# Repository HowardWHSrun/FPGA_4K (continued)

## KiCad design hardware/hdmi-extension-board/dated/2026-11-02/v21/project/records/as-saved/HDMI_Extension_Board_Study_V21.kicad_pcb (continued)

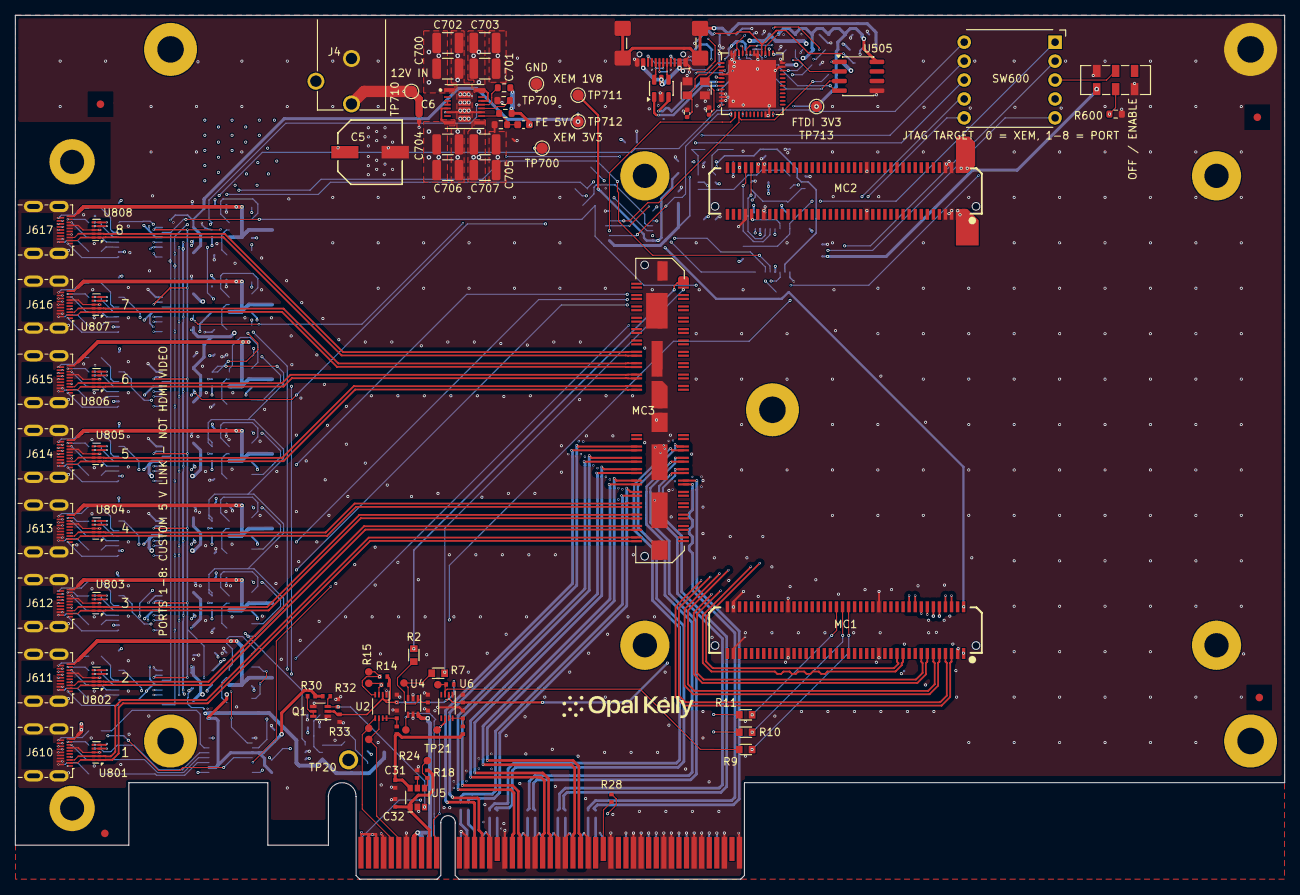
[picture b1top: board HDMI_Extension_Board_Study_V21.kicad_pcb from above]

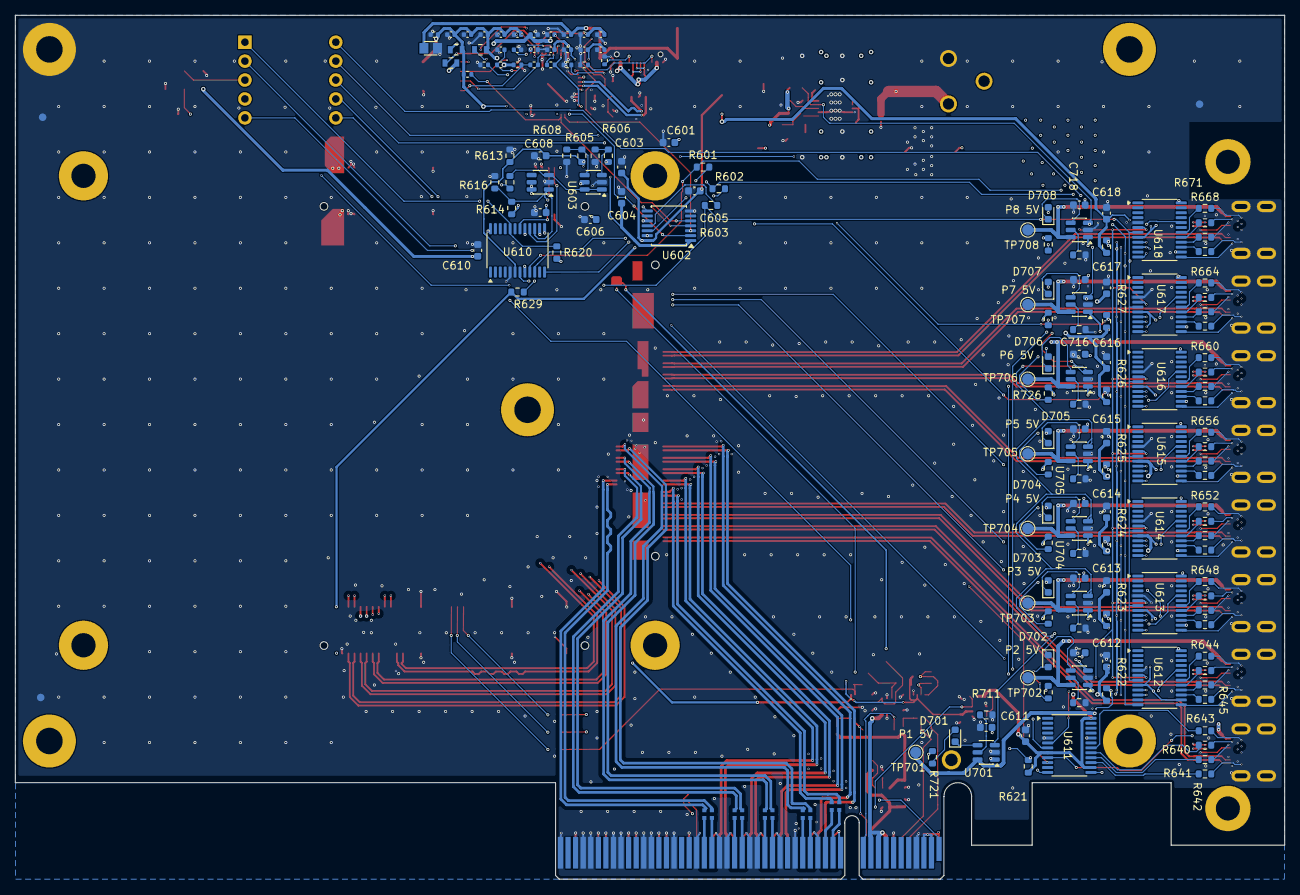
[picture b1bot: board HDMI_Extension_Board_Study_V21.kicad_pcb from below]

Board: 6 copper layers, 167.6 x 114.1 mm, 275 parts (173 on the bottom side), 254 nets.

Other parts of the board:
*: Opal Kelly Logo; BRK_Logo_c689e08d
FID1, FID5, FID6, FID7: FIDUCIAL; BRK_FID1
FID2: FIDUCIAL; BRK_FID2
FID3: FIDUCIAL; BRK_FID3
FID4: FIDUCIAL; BRK_FID4

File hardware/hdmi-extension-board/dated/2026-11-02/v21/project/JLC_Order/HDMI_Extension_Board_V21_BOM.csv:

Comment,Designator,Footprint,JLCPCB Part #
C0402C104K8PACTU,"C7,C8,C9,C10,C11,C12,C13,C14,C15,C16,C17,C18,C19,C20,C27,C28,C31,C32,C501,C502,C505,C508,C509,C510,C511,C514,C516,C517,C518",BRK8310_C10,C2649544
EEE-FK1E221P,C5,BRK_C5,C128511
4.7u,C500,C500,C23733
18p,"C503,C504",C504,C22442494
100n,C506,C506,C1525
4.7u,"C507,C512,C513,C515",C515,C87147
10n,C519,C519,C2649513
TMK105BJ104KV-F,C6,BRK_C6,C77014
2.2u,"C601,C603",C_0603_1608Metric,C100082
100nF,"C604,C605,C606,C609,C610,C611,C612,C613,C614,C615,C616,C617,C618,C711,C712,C713,C714,C715,C716,C717,C718",C_0603_1608Metric,C14663
1n,C608,C_0603_1608Metric,C8808
10uF,"C700,C701,C702,C703",C_1210_3225Metric,C77102
47uF,"C704,C705,C706,C707",C_1210_3225Metric,C77101
22pF,C708,C_0603_1608Metric,C376775
USBLC6-2SC6,D500,D500,C7519
RED,"D701,D702,D703,D704,D705,D706,D707,D708",LED_0603_1608Metric,C94869
600R,"FB500,FB501,FB502",FB502,C19330
220R @100MHz,FB503,FB503,C85840
PJ-102AH,J4,BRK_J4,C3096093
USB4110-GF-A,J500,J500,C5143397
467651001,"J610,J611,J612,J613,J614,J615,J616,J617",HDMI_Micro-D_Molex_46765-1xxx,C563878
BTE-040-01-F-D-A,"MC1,MC2",BRK_MC1,C2914307
QTH-040-01-F-D-DP-A,MC3,BRK_MC3,C7330812
SI1922EDH-T1-GE3,Q1,BRK8310_Q1,C141538
CRCW06030000Z0EA,"R2,R7,R9,R10,R11",BRK8310_R10,C844915
CRCW0402200KFKED,"R13,R23",BRK8310_R13,C482093
CRCW04024K75FKED,"R14,R15,R30,R31",BRK8310_R14,C844510
CRCW0402100KFKED,"R18,R24,R25,R32,R33,R502,R503",BRK8310_R18,C481918
CRCW04020000Z0ED,R28,BRK8310_R28,C190119
5.1k 1%,"R500,R501",R501,C2076825
2k,R504,R504,C482125
10k,"R505,R506,R509",R509,C71617
12k 1%,R507,R507,C481938
3.3k,"R600,R721,R722,R723,R724,R725,R726,R727,R728",R_0603_1608Metric,C22978
22R,"R601,R602,R603",R_0603_1608Metric,C23345
301k,R605,R_0603_1608Metric,C23026
100k,"R606,R608,R616",R_0603_1608Metric,C25803
402k,R607,R_0603_1608Metric,C23048
68k,R613,R_0603_1608Metric,C23231
4.7k,R614,R_0603_1608Metric,C23162
12k,R615,R_0603_1608Metric,C22790
10k,"R620,R621,R622,R623,R624,R625,R626,R627,R628",R_0603_1608Metric,C25804
1k,R629,R_0603_1608Metric,C21190
100R,"R640,R641,R642,R643,R644,R645,R646,R647,R648,R649,R650,R651,R652,R653,R654,R655,R656,R657,R658,R659,R660,R661,R662,R663,R664,R665,R666,R667,R668,R669,R670,R671",R_0603_1608Metric,C22775
40.2k,R700,R_0603_1608Metric,C137723
10k,"R701,R703",R_0603_1608Metric,C98220
13k,R702,R_0603_1608Metric,C22797
37.4k,"R711,R712,R713,R714,R715,R716,R717,R718",R_0603_1608Metric,C163425
SRBQ490100,SW600,ALPS_SRBQ490100_1P9T,C370985
JS202011JCQN,SW601,SW700,C221665
PCA9306DCUR,"U2,U6",BRK8310_U2,C33196
SN74AXC1T45DCK,U4,BRK8310_U4,C2677392
AP22653AW6-7,U5,BRK8310_U5,C1511768
FT232HQ-REEL,U501,U501,C82158
93LC56BT-I/SN,U505,SOIC-8_3.9x4.9mm_P1.27mm,C6164
TXU0304PWR,U602,TSSOP-14_4.4x5mm_P0.65mm,C4364118
TPS3700DDCR,U603,SOT-23-6,C33002
TPS3808G30DBVR,U605,SOT-23-6,C189211
TS3A27518EPWR,"U610,U611,U612,U613,U614,U615,U616,U617,U618",TSSOP-24_4.4x7.8mm_P0.65mm,C443721
TPSM63606RDLR,U700,TI_TPSM63606_RDL0020A_EVM,C5219325
TPS2553DBVR,"U701,U702,U703,U704,U705,U706,U707,U708",SOT-23-6,C55266
TPD4E02B04DQAR,"U801,U802,U803,U804,U805,U806,U807,U808",USON-10_2.5x1.0mm_P0.5mm,C106794
7U12000E18UCG 12MHz,Y500,Y500,C524717

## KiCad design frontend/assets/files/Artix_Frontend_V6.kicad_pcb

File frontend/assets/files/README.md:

# Frontend FPGA Board V6 — full KiCad project

Captured 2026-11-01T20:25:31.504070-06:00. Open `Artix_Frontend_V6/Artix_Frontend_V6.kicad_pro` in KiCad 10.0.6 or newer after extracting the entire ZIP. Keep the PCB, schematic, settings, rules, symbol and footprint libraries, library tables and model folders together.

Artix-7 frontend with Micro-HDMI, mezzanine interfaces and 5 V input conversion. Unrouted placement study; package selection, regulator layout, timing and power integrity remain under review.

This package includes the complete saved project and available 3D model dependencies. Local model paths are retained or made relative for portability. Historical native filenames and library identifiers remain intact. Editor caches, lock files and automatic backups are excluded. Model coverage and unresolved paths are recorded in `package-manifest.json`; nominal or substitute models are not proof of assembled fit.

Native snapshot: 185 schematic components, 185 PCB footprints, 10 copper layers, 0 track/via objects and 0 copper zones. Check reports: 0 DRC errors, 0 DRC warnings, 499 unconnected-item reports, 0 schematic/PCB parity findings. These are saved-rule CAD checks, not hardware or fabrication qualification; ignored categories remain in the check summary.

Native source and manufacturer identifiers are retained. Existing third-party library and model terms continue to apply; this package grants no new rights to those materials. KiCad library license: https://www.kicad.org/libraries/license/ . Engineering references remain in the schematic and source fields.

[Download full KiCad ZIP](Frontend_FPGA_Board_V6_Full_KiCad.zip) · [Schematic PDF](../schematic-v6.pdf)

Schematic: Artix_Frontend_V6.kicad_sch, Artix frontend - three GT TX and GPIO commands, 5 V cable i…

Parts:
C1, C2, C12, C13, C21, C22, C85, C86: 22uF; C_0603_1608Metric; Voltage 6.3 V; Tolerance 20%; MPN GRM188R60J226MEA0D
C3, C14, C23, C87: 22pF; C_0201_GRM03_Murata_0p22Gap; Voltage 50 V; Tolerance 2%; MPN GRM0335C1H220GA01D
C4, C10, C89: 100uF; C_0805_2012Metric; Voltage 6.3 V; Tolerance 20%; MPN GRM21BR60J107ME15L
C5, C6, C16, C17, C24, C25, C30, C31, C36, C37, C43, C44, C45, C47, C48, C49, C51, C54, C90, C94, C95, C96, C101: 4.7uF; C_0402_1005Metric; Voltage 6.3 V; Tolerance 20%; MPN GRM155R60J475ME47D
C7, C8, C9, C11, C18, C19, C20, C26, C27, C28, C29, C32, C33, C34, C35, C38, C39, C40, C52, C53, C55, C56, C57, C58, C80, C91, C92, C93, C97, C98, C99, C100: 470nF; C_0201_GRM03_Murata_0p22Gap; Voltage 6.3 V; Tolerance 20%; MPN GRM033R60J474ME90D
C15, C42, C59: 47uF; C_0805_2012Metric; Voltage 6.3 V; Tolerance 20%; MPN CC0805MKX5R5BB476
C46, C50: 10nF; C_0201_GRM03_Murata_0p22Gap; Voltage 10 V; Tolerance 10%; MPN GRM033R71A103KA01D
C60, C63, C78, C79, C81, C82, C83, C88, C105, C106: 100nF; C_0201_GRM03_Murata_0p22Gap; Voltage 10 V; Tolerance 10%; MPN GRM033R61A104KE15D
C61, C84: 1uF; C_0402_1005Metric; Voltage 10 V; Tolerance 10%; MPN GRM155C81A105KA12D
C62: 220nF; C_0201_GRM03_Murata_0p22Gap; Voltage 6.3 V; Tolerance 10%; MPN GRM033R60J224KE90D
C75, C76, C102, C104: 22uF / 6.3V; C_0603_1608Metric; Voltage 6.3 V; Tolerance 20%; MPN GRM188R60J226MEA0D
C77: 22nF / 50V; C_0402_1005Metric; Voltage 50V; Tolerance Not stated by Trenz; exact candidate pe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
C103: 470nF / 6.3V; C_0201_GRM03_Murata_0p22Gap; Voltage 6.3 V; Tolerance 20%; MPN GRM033R60J474ME90D
C200, C201, C202, C203, C204, C205: 100nF; C_0402_1005Metric
C206, C207, C208: 22uF / 10V; C_0805_2012Metric; Voltage 10 V; Tolerance 20%; MPN GRM21BR61A226ME44L
J1, J2: DF40C-60DS-0.4V(51); Hirose_DF40C-60DS-0.4V_2x30_P0.4mm; MPN DF40C-60DS-0.4V(51)
J3: Micro-HDMI 467651001; Molex_MicroHDMI_46765_1xxx; MPN 467651001
L1, L2, L3, L4: MPZ0603S121HT000; TDK_MPZ0603S121HT000_0201_Land_0p25x0p30_Gap0p30; MPN MPZ0603S121HT000
R1, R4, R5, R41, R55: 200k; R_0402_1005Metric; Tolerance 1%; Voltage_rating 50 V; MPN RC0402FR-07200KL
R2: 301k; R_0402_1005Metric; Tolerance 1%; Voltage_rating 50 V; MPN RC0402FR-07301KL
R3, R9, R11, R12, R14, R17, R18, R19, R22, R38, R43: 4.99k; R_0402_1005Metric; Tolerance 1%; Voltage_rating 50 V; MPN RC0402FR-074K99L
R7: 150k; R_0402_TE_CPF_Reflow_0p50Gap; Tolerance 0.1%; Voltage_rating 25 V; MPN CPF0402B150KE
R8: 100k; R_0402_TE_CPF_Reflow_0p50Gap; Tolerance 0.1%; Voltage_rating 25 V; MPN CPF0402B100KE
R10: 1.3k; R_0402_1005Metric; Tolerance 1%; Voltage_rating 50 V; MPN RC0402FR-071K3L
R13: 2.49k; R_0402_1005Metric; Tolerance 1%; Voltage_rating 50 V; MPN RC0402FR-072K49L
R16, R56: 100R; R_0201_ERA1A_Panasonic_0p30Gap; Tolerance 0.1%; Voltage_rating 25 V; MPN ERA1AEB101C
R20, R21, R49, R50: 4.7k; R_0201_ERA1A_Panasonic_0p30Gap; Tolerance 0.1%; MPN ERA1AEB472C
R25: 470R; R_0402_1005Metric; Tolerance 1%; Voltage_rating 50 V; MPN RC0402FR-07470RL
R27: 1k; R_0201_ERA1A_Panasonic_0p30Gap; Tolerance 0.1%; MPN ERA1AEB102C
R37: 24k / 1%; R_0402_1005Metric; Tolerance 1%; Voltage_rating Exact candidate not selected; source me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
R42: 150k; R_0402_1005Metric; Tolerance 1%; Voltage_rating 50 V; MPN RC0402FR-07150KL
R44: 33R; R_0201_0603Metric; Tolerance 1%; Voltage_rating 25 V; MPN RC0201FR-0733RL
R45: 4.64k; R_0201_ERA1A_Panasonic_0p30Gap; Tolerance 0.1%; MPN ERA1AEB4641C
R46, R47, R48: 10k; R_0201_ERA1A_Panasonic_0p30Gap; Tolerance 0.1%; MPN ERA1AEB103C
R51, R52, R53: 47k; R_0201_ERA1A_Panasonic_0p30Gap; Tolerance 0.1%; MPN ERA1AEB473C
R54: 22k; R_0201_ERA1A_Panasonic_0p30Gap; Tolerance 0.1%; MPN ERA1AEB223C
R57: 10k; R_0402_1005Metric; Tolerance 1%; MPN RC0402FR-0710KL
R58: 4.99k; R_0402_1005Metric; Tolerance 1%; MPN RC0402FR-074K99L
R59: 200k; R_0402_1005Metric; Tolerance 1%; MPN RC0402FR-07200KL
R60: 44.2k; R_0402_1005Metric; Tolerance 1%; MPN RC0402FR-0744K2L
TP1, TP2, TP3, TP4, TP5, TP6, TP7, TP8, TP9, TP10, TP11, TP12, TP13, TP14: 0.6mm COPPER; TestPoint_Pad_D0.6mm_Edge_NoPaste
U1: XC7A35T-2CSG325I; Xilinx_CSG325; MPN XC7A35T-2CSG325I
U2, U3, U4, U13, U16: MPM3834CGPA; MPM3834C_ECLGA14_2.5x2.5mm; MPN MPM3834CGPA-Z
U5, U6: TPS74801DRCRM3; VSON-10-1EP_3x3mm_P0.5mm_EP1.65x2.4mm; MPN TPS74801DRCRM3
U7: W25Q128JWUUIQ; ISSI_USON8_4x3mm_T; MPN W25Q128JWUUIQ
U8: SN74AVC4T774RSVR / SPI x1; TI_RSV_UQFN16_1.8x2.6mm_P0.4mm; MPN SN74AVC4T774RSVR
U10: MP5077GG-Z; MPS_MP5077_QFN12_2x2mm_P0.4mm; MPN MP5077GG-Z
U11: 74AUP2G07GM / dual reset OD; Nexperia_SOT886_XSON6_1x1.45mm; MPN 74AUP2G07GM,115
U12: TPS389001 / timed rail-ready reset; TI_DSE0006A_WSON6_1p5x1p5_P0p5_Manufacturer; MPN TPS389001DSER
U14: SN74AUP1G14 / SPI OE; TI_DCK_SC70_5; MPN SN74AUP1G14DCKR
U15: SN74AXC1T45DCKR; SOT-363_SC-70-6; MPN SN74AXC1T45DCKR
Y1: AX3DAF1-125.0000T3 / 125 MHz; Abracon_AX3_3225_6pin; Voltage 3.3 V filtered from SWITCHED_3V3 by L4; MPN AX3DAF1-125.0000T3
Y2: SiT1615A / 25 MHz / 1.5 V; SiTime_2016_4pin; MPN SiT1615AE-78-15N-25.000000G

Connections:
1V4_GTP_IN: C43.2, C47.2, C86.1, C87.1, R41.1, U5.1 (IN), U5.2 (IN), U6.1 (IN), U6.2 (IN), U13.6 (OUT_S), U13.9 (OUT), U13.10 (OUT)
/AC_IN_ANALOG_RESERVED: J2.60
/ASIC1_CLK32MHz_Out: J1.9, U1.P14 (L12P_T1_MRCC)
/ASIC1_DATA1: J1.1, U1.J14 (L5P_T0_D06)
/ASIC1_DATA2: J1.2, U1.V16 (L18P_T2_A12_D28)
/ASIC1_DATA3: J1.3, U1.V17 (L18N_T2_A11_D27)
/ASIC1_DATA4: J1.4, U1.K15 (L5N_T0_D07)
/ASIC1_DATA5: J1.5, U1.K17 (L4P_T0_D04)
/ASIC1_DATA6: J1.6, U1.K18 (L3N_T0_DQS_EMCCLK)
/ASIC1_DATA7: J1.7, U1.L14 (IO0)
/ASIC1_DATA8: J1.8, U1.L18 (L4N_T0_D05)
/ASIC1_READ: J1.10, U1.M14 (L8P_T1_D11)
/ASIC1_SYNC: J1.11, U1.M16 (L7P_T1_D09)
/ASIC2_CLK32MHz_Out: J1.20, U1.T14 (L13P_T2_MRCC)
/ASIC2_DATA1: J1.12, U1.M17 (L7N_T1_D10)
/ASIC2_DATA2: J1.13, U1.N14 (L8N_T1_D12)
/ASIC2_DATA3: J1.14, U1.N16 (L9P_T1_DQS)
/ASIC2_DATA4: J1.15, U1.N17 (L9N_T1_DQS_D13)
/ASIC2_DATA5: J1.16, U1.N18 (L10P_T1_D14)
/ASIC2_DATA6: J1.17, U1.P16 (L11N_T1_SRCC)
/ASIC2_DATA7: J1.18, U1.P18 (L10N_T1_D15)
/ASIC2_DATA8: J1.19, U1.R13 (L19P_T3_A10_D26)
/ASIC2_READ: J1.21, U1.R15 (L12N_T1_MRCC)
/ASIC2_SYNC: J1.22, U1.R17 (L14N_T2_SRCC)
/ASIC3_CLK32MHz_Out: J1.32, U1.P15 (L11P_T1_SRCC)
/ASIC3_DATA1: J1.23, U1.R18 (L15P_T2_DQS_RDWR_B)
/ASIC3_DATA2: J1.24, U1.T12 (L22P_T3_A05_D21)
/ASIC3_DATA3: J1.25, U1.T15 (L13N_T2_MRCC)
/ASIC3_DATA4: J1.26, U1.T17 (L16P_T2_CSI_B)
/ASIC3_DATA5: J1.27, U1.T18 (L15N_T2_DQS_DOUT_CSO_B)
/ASIC3_DATA6: J1.28, U1.U9 (L24P_T3_A01_D17)
/ASIC3_DATA7: J1.29, U1.U10 (IO25)
/ASIC3_DATA8: J1.31, U1.U11 (L23P_T3_A03_D19)
/ASIC3_READ: J1.33, U1.U12 (L22N_T3_A04_D20)
/ASIC3_SYNC: J1.34, U1.U14 (L20P_T3_A08_D24)
/ASIC4_CLK32MHz_Out: J1.43, U1.E13 (L12P_T1_MRCC)
/ASIC4_DATA1: J1.35, U1.A9 (L3N_T0_DQS_AD1N)
/ASIC4_DATA2: J1.36, U1.A10 (L5N_T0_AD9N)
/ASIC4_DATA3: J1.37, U1.A12 (L7N_T1_AD2N)
/ASIC4_DATA4: J1.38, U1.A13 (L8P_T1_AD10P)
/ASIC4_DATA5: J1.39, U1.A14 (L8N_T1_AD10N)
/ASIC4_DATA6: J1.40, U1.A15 (L10N_T1_AD11N)
/ASIC4_DATA7: J1.41, U1.A17 (L15N_T2_DQS_ADV_B)
/ASIC4_DATA8: J1.42, U1.B9 (L3P_T0_DQS_AD1P)
/ASIC4_READ: J1.44, U1.B10 (L5P_T0_AD9P)
/ASIC4_SYNC: J1.45, U1.B11 (L4N_T0)
/ASIC5_CLK32MHz_Out: J2.9, U1.E15 (L13P_T2_MRCC)
/ASIC5_DATA1: J2.1, U1.B12 (L7P_T1_AD2P)
/ASIC5_DATA2: J2.2, U1.B14 (L10P_T1_AD11P)
/ASIC5_DATA3: J2.3, U1.B15 (L9N_T1_DQS_AD3N)
/ASIC5_DATA4: J2.4, U1.B16 (L15P_T2_DQS)
/ASIC5_DATA5: J2.5, U1.B17 (L16N_T2_A27)
/ASIC5_DATA6: J2.6, U1.C8 (L1N_T0_AD0N)
/ASIC5_DATA7: J2.7, U1.C9 (L2N_T0_AD8N)
/ASIC5_DATA8: J2.8, U1.C11 (L4P_T0)
/ASIC5_READ: J2.10, U1.C13 (L11N_T1_SRCC)
/ASIC5_SYNC: J2.11, U1.C14 (L9P_T1_DQS_AD3P)
/ASIC6_CLK32MHz_Out: J2.20, U1.D13 (L11P_T1_SRCC)
/ASIC6_DATA1: J2.12, U1.C16 (L16P_T2_A28)
/ASIC6_DATA2: J2.13, U1.C17 (L18P_T2_A24)
/ASIC6_DATA3: J2.14, U1.C18 (L18N_T2_A23)
/ASIC6_DATA4: J2.15, U1.D8 (L1P_T0_AD0P)
/ASIC6_DATA5: J2.16, U1.D9 (L2P_T0_AD8P)
/ASIC6_DATA6: J2.17, U1.D10 (IO0)
/ASIC6_DATA7: J2.18, U1.D11 (L6P_T0)
/ASIC6_DATA8: J2.19, U1.D14 (L12N_T1_MRCC)
/ASIC6_READ: J2.21, U1.D15 (L13N_T2_MRCC)
/ASIC6_SYNC: J2.22, U1.D16 (L14N_T2_SRCC)
/ASIC7_CLK32MHz_Out: J2.32, U1.P4 (L12P_T1_MRCC)
/ASIC7_DATA1: J2.23, U1.J4 (L2N_T0)
/ASIC7_DATA2: J2.24, U1.J5 (L2P_T0)
/ASIC7_DATA3: J2.25, U1.J6 (IO0)
/ASIC7_DATA4: J2.26, U1.K1 (L3N_T0_DQS)
/ASIC7_DATA5: J2.27, U1.K2 (L3P_T0_DQS)
/ASIC7_DATA6: J2.28, U1.K3 (L4P_T0)
/ASIC7_DATA7: J2.29, U1.K5 (L1N_T0)
/ASIC7_DATA8: J2.31, U1.K6 (L1P_T0)
/ASIC7_READ: J2.33, U1.L2 (L4N_T0)
/ASIC7_SYNC: J2.34, U1.L3 (L5N_T0)
/ASIC8_CLK32MHz_Out: J2.43, U1.R2 (L13P_T2_MRCC)
/ASIC8_DATA1: J2.35, U1.L4 (L5P_T0)
/ASIC8_DATA2: J2.36, U1.L5 (L6P_T0)
/ASIC8_DATA3: J2.37, U1.M1 (L7N_T1)
/ASIC8_DATA4: J2.38, U1.M2 (L7P_T1)
/ASIC8_DATA5: J2.39, U1.M4 (L10P_T1)
/ASIC8_DATA6: J2.40, U1.M6 (L8P_T1)
/ASIC8_DATA7: J2.41, U1.N1 (L9P_T1_DQS)
/ASIC8_DATA8: J2.42, U1.N2 (L11N_T1_SRCC)
/ASIC8_READ: J2.44, U1.N4 (L10N_T1)
/ASIC8_SYNC: J2.45, U1.N6 (L8N_T1)
/CHIP_RESET_SHARED: J1.56, U1.T3 (L17N_T2)
/CLK25_RAW: R44.1, Y2.3 (OUT)
/CLK25_VDD: C88.1, L3.2, Y2.4 (VDD)
/FB_GTP_1V4: C87.2, R41.2, R42.1, U13.5 (FB)
/FB_VIN_3V3: R59.2, R60.1, U16.5 (FB)
/FE_RESET_SHARED: J1.57, U1.T4 (L17P_T2)
/GPIO_CMD_N: J3.14 (GPIO_CMD_N), U1.V2 (L16N_T2)
/GPIO_CMD_P: J3.12 (GPIO_CMD_P), U1.V3 (L16P_T2)
/IMP_TST_SHARED: J1.58, U1.D18 (L17N_T2_A25)
/NONSTIM_BOARD1_SPI_DL: J1.54, U1.T5 (L21N_T3_DQS)
/NONSTIM_BOARD1_SPI_DR: J1.55, U1.E17 (L17P_T2_A26)
/NONSTIM_BOARD2_SPI_DL: J2.54, U1.T7 (L22N_T3)
/NONSTIM_BOARD2_SPI_DR: J2.55, U1.E18 (L24N_T3_RS0)
/STIM_CHIP1_SPI_DL: J1.50, U1.U2 (L15P_T2_DQS)
/STIM_CHIP1_SPI_DR: J1.51, U1.U15 (L17P_T2_A14_D30)
/STIM_CHIP2_SPI_DL: J1.52, U1.F15 (L21N_T3_DQS_A18)
/STIM_CHIP2_SPI_DR: J1.53, U1.U4 (L18P_T2)
/STIM_CHIP3_SPI_DL: J2.50, U1.U16 (L17N_T2_A13_D29)
/STIM_CHIP3_SPI_DR: J2.51, U1.F17 (L24P_T3_RS1)
/STIM_CHIP4_SPI_DL: J2.52, U1.U5 (L20N_T3)
/STIM_CHIP4_SPI_DR: J2.53, U1.U17 (L16N_T2_A15_D31)
BOARD1_CLK: J1.46, U1.P1 (L9N_T1_DQS)
BOARD1_SPI_CLK: J1.48, U1.P3 (L12N_T1_MRCC)
BOARD2_CLK: J1.47, U1.P6 (L19P_T3)
BOARD2_SPI_CLK: J1.49, U1.R1 (L13N_T2_MRCC)
BOARD3_CLK: J2.46, U1.R5 (L21P_T3_DQS)
BOARD3_SPI_CLK: J2.48, U1.R6 (IO25)
BOARD4_CLK: J2.47, U1.R7 (L22P_T3)
BOARD4_SPI_CLK: J2.49, U1.T2 (L14N_T2_SRCC)
BOOT_RAILS_PG_3V3: R9.2, TP10.1 (PAD_1), U4.11 (PG), U5.3 (PG), U12.3 (MR_PG)
BOOT_RESET_N: R47.2, U11.1 (1A_RESET_N), U11.3 (2A_RESET_N), U12.6 (RESET_N_OD), U14.2 (A_RESET_N)
CABLE_TARGET_SENSE: J3.1 (SENSE), R27.2
CLK25_PL: R44.2, U1.N3 (L11P_T1_SRCC)
EN_GTPWR_1V5: R58.2, U1.M15 (L6N_T0_D08_VREF), U15.3 (A)
EN_GTPWR_3V3: R57.1, U13.3 (EN), U15.4 (B)
FLASH_CS_N_1V8: R22.2, U7.1 (CE#), U8.11 (B2_CS)
FLASH_DQ0_1V8: R53.2, U7.5 (SI_/_DQ0), U8.10 (B3_MOSI)
FLASH_DQ1_1V8: R51.1, U7.2 (SO_/_DQ1), U8.9 (B4_MISO)
FLASH_HOLD_N_1V8: R21.2, U7.7 (HOLD#_/_DQ3)
FLASH_READY_SENSE: R45.2, R46.1, U12.1 (SENSE_DIV)
FLASH_SCK_1V8: R52.1, U7.6 (SCK), U8.12 (B1_SCK)
FLASH_TRANSLATOR_OE_N: R48.2, U8.7 (OE_N), U14.4 (Y_OE_N)
FLASH_WP_N_1V8: R20.2, U7.3 (WP#_/_DQ2)
FPGA_DONE: R38.2, TP12.1 (PAD_1), U1.F12 (DONE_0)
FPGA_INIT_B: R18.2, TP11.1 (PAD_1), U1.T10 (INIT_B_0), U11.4 (2Y_INIT_OD)
FPGA_JTAG_TCK: J3.17 (TCK), U1.F8 (TCK_0)
FPGA_JTAG_TDI: J3.15 (TDI), U1.T9 (TDI_0)
FPGA_JTAG_TDO: J3.18 (TDO), U1.T8 (TDO_0)
FPGA_JTAG_TMS: J3.2 (TMS), U1.R8 (TMS_0)
FPGA_PROGRAM_B: R17.2, U1.P10 (PROGRAM_B_0), U11.6 (1Y_PROGRAM_OD)
FPGA_PUDC_B: R25.2, U1.J18 (L3P_T0_DQS_PUDC_B)
FPGA_QSPI_CCLK: R49.2, U1.E8 (CCLK_0), U8.1 (A1_CCLK)
FPGA_QSPI_CS_N: R19.2, U1.L15 (L6P_T0_FCS_B), U8.2 (A2_CS)
FPGA_QSPI_DQ0: R50.2, U1.K16 (L1P_T0_D00_MOSI), U8.3 (A3_MOSI)
FPGA_QSPI_DQ1: R54.1, U1.L17 (L1N_T0_D01_DIN), U8.4 (A4_MISO)
GND: C1.2, C2.2, C4.2, C5.2, C6.2, C7.2, C8.2, C9.2, C10.2, C11.2, C12.2, C13.2, C15.2, C16.2, C17.2, C18.2, C19.2, C20.2, C21.2, C22.2, C24.2, C25.2, C26.2, C27.2, C28.2, C29.2, C30.2, C31.2, C32.2, C33.2, C34.2, C35.2, C36.2, C37.2, C38.2, C39.2, C40.2, C42.2, C43.1, C44.2, C45.2, C46.2, C47.1, C48.2, C49.2, C50.2, C51.2, C52.2, C53.2, C54.2, C55.2, C56.2, C58.2, C59.2, C60.2, C61.2, C62.2, C63.2, C75.2, C76.2, C77.2, C80.2, C81.2, C82.2, C83.2, C84.2, C85.2, C86.2, C88.2, C89.2, C90.2, C91.2, C92.2, C93.2, C94.2, C95.2, C96.2, C97.2, C98.2, C99.2, C100.2, C101.2, C102.2, C103.2, C104.2, C105.2, C106.2, C206.2, C207.2, C208.2, J1.30, J2.30, J3.4 (GND), J3.7 (GND), J3.10 (GND), J3.13 (GND), J3.16 (GND), J3.SH (SHIELD), L2.1, R2.2, R5.2, R8.2, R11.2, R14.2, R37.2, R42.2, R46.2, R51.2, R52.2, R54.2, R55.2, R57.2, R60.2, TP1.1 (PAD_1), TP13.1 (PAD_1), U1.A1 (GND_[75_balls]), U1.A3 (MGTPRXN1_216), U1.A4 (MGTPRXP1_216), U1.A5 (GND), U1.A7 (GND), U1.A8 (GND), U1.A11 (GND), U1.A18 (GND), U1.B3 (GND), U1.B7 (GND), U1.B8 (GND), U1.B18 (GND), U1.C2 (GND), U1.C3 (MGTPRXN2_216), U1.C4 (MGTPRXP2_216), U1.C6 (GND), U1.C7 (GND), U1.C15 (GND), U1.D3 (GND), U1.D4 (GND), U1.D7 (GND), U1.D12 (GND), U1.E2 (GND), U1.E3 (MGTPRXN0_216), U1.E4 (MGTPRXP0_216), U1.E6 (GND), U1.E7 (GND), U1.E9 (GND), U1.E12 (CFGBVS_0), U1.F4 (GND), U1.F6 (GND), U1.F10 (GND), U1.F13 (M2_0), U1.F16 (GND), U1.G1 (GND), U1.G3 (MGTPRXN3_216), U1.G4 (MGTPRXP3_216), U1.G5 (GND), U1.G6 (GND), U1.G7 (GND), U1.G9 (GND), U1.G11 (GND), U1.G13 (GND), U1.H3 (GND), U1.H4 (GND), U1.H5 (GND), U1.H6 (GND), U1.H8 (GND), U1.H10 (GND), U1.H12 (GND), U1.J1 (GND), U1.J2 (GND), U1.J3 (GND), U1.J7 (GND), U1.J11 (GND), U1.J13 (GND), U1.J17 (GND), U1.K4 (GND), U1.K8 (GND), U1.K12 (GND), U1.K14 (GND), U1.L1 (GND), U1.L7 (GND), U1.L11 (GND), U1.L13 (GND), U1.M8 (GND), U1.M9 (DXN_0), U1.M10 (DXP_0), U1.M12 (GND), U1.M18 (GND), U1.N5 (GND), U1.N7 (GND), U1.N9 (GND), U1.N11 (GND), U1.N13 (GND), U1.N15 (GND), U1.P2 (GND), U1.P8 (GND), U1.P12 (GND), U1.R9 (GND), U1.R11 (M1_0), U1.T6 (GND), U1.T16 (GND), U1.U3 (GND), U1.U13 (GND), U1.V1 (GND), U1.V10 (GND), U1.V18 (GND), U2.2 (PGND), U2.4 (AGND), U2.7 (PGND), U2.8 (PGND), U3.2 (PGND), U3.4 (AGND), U3.7 (PGND), U3.8 (PGND), U4.2 (PGND), U4.4 (AGND), U4.7 (PGND), U4.8 (PGND), U5.6 (GND), U5.11 (GND_EP), U6.6 (GND), U6.11 (GND_EP), U7.4 (GND_/_optional_tabs), U8.6 (DIR4_L), U8.8 (GND), U10.2 (GND), U11.2 (GND), U12.2 (GND), U13.2 (PGND), U13.4 (AGND), U13.7 (PGND), U13.8 (PGND), U14.3 (GND), U15.2 (GND), U16.2 (PGND), U16.4 (AGND), U16.7 (PGND), U16.8 (PGND), Y1.3 (GND), Y2.2 (GND)
GNDADC_XADC: C57.2, L2.2, U1.J9 (GNDADC_0), U1.K9 (VREFN_0), U1.K10 (VP_0), U1.L9 (VN_0), U1.L10 (VREFP_0)
GTP_REFCLK1_N: C79.2, U1.B5 (MGTREFCLK1N_216)
GTP_REFCLK1_P: C78.2, U1.B6 (MGTREFCLK1P_216)
GTP_TX0_N: C201.1, J3.5 (TX0_REC_N)
GTP_TX0_P: C200.1, J3.3 (TX0_REC_P)
MGTAVCC_1V0: C45.1, C51.1, C52.1, C53.1, R10.1, TP7.1 (PAD_1), U1.B4 (MGTAVCC), U1.C5 (MGTAVCC), U1.E5 (MGTAVCC), U1.F5 (MGTAVCC), U5.9 (OUT), U5.10 (OUT)
MGTAVTT_1V2: C49.1, C54.1, C55.1, C56.1, R13.1, R16.1, TP8.1 (PAD_1), U1.A2 (MGTAVTT), U1.C1 (MGTAVTT), U1.E1 (MGTAVTT), U1.F3 (MGTAVTT), U1.G2 (MGTAVTT), U6.9 (OUT), U6.10 (OUT)
unnamed: C203.1, J3.8 (TX1_REC_N)
unnamed: C202.1, J3.6 (TX1_REC_P)
unnamed: C205.1, J3.11 (TX2_REC_N)
unnamed: C204.1, J3.9 (TX2_REC_P)
unnamed: C201.2, U1.H1 (MGTPTXN0_216)
unnamed: C203.2, U1.F1 (MGTPTXN1_216)
unnamed: C205.2, U1.D1 (MGTPTXN2_216)
unnamed: C200.2, U1.H2 (MGTPTXP0_216)
unnamed: C202.2, U1.F2 (MGTPTXP1_216)
unnamed: C204.2, U1.D2 (MGTPTXP2_216)
unnamed: R16.2, U1.A6 (MGTRREF_216)
unnamed: C3.2, R1.2, R2.1, U2.5 (FB)
unnamed: C14.2, R4.2, R5.1, R55.1, U3.5 (FB)
unnamed: C23.2, R7.2, R8.1, U4.5 (FB)
unnamed: R10.2, R11.1, U5.8 (FB)
unnamed: C46.1, U5.7 (SS)
unnamed: R13.2, R14.1, U6.8 (FB)
unnamed: C50.1, U6.7 (SS)
unnamed: R37.1, U10.4 (ILIM)
unnamed: C77.1, U10.5 (SS)
unnamed: C84.1, U12.5 (CT)
OSC125_3V3: C80.1, C81.1, L4.2, Y1.1 (OE), Y1.6 (VDD)
OSC125_N: C79.1, R56.2, Y1.5 (OUTN)
OSC125_P: C78.1, R56.1, Y1.4 (OUTP)
PG_CORE_1V0: R3.2, U2.11 (PG), U3.3 (EN), U4.3 (EN), U10.1 (EN)
PG_GTP_1V4: R43.2, U6.5 (EN), U13.11 (PG)
PG_MGT_1V2: R12.2, U5.5 (EN), U6.3 (PG)
SPI_LATCH_SHARED: J1.59, U1.U1 (L15N_T2_DQS)
STIM_CHB_SHARED: J2.59, U1.F14 (L22N_T3_A16)
STIM_CLK_SHARED: J2.56, U1.G14 (L22P_T3_A17)
STIM_EN_SHARED: J2.58, U1.U6 (L20P_T3)
STIM_START_SHARED: J2.57, U1.V9 (L24N_T3_A00_D16)
SWITCHED_3V3: C76.1, C104.1, C106.1, L4.1, TP3.1 (PAD_1), U10.7 (VOUT), U10.8 (VOUT), U10.9 (VOUT), U10.10 (VOUT), U15.6 (VCCB)
VCCADC_1V8: C57.1, L1.2, U1.J10 (VCCADC_0)
VCCAUX_1V8: C13.1, C14.1, C15.1, C16.1, C17.1, C18.1, C19.1, C20.1, C58.1, C59.1, C60.1, C62.1, C94.1, C95.1, C96.1, C97.1, C98.1, C99.1, C100.1, L1.1, R4.1, R17.1, R18.1, R20.1, R21.1, R22.1, R27.1, R38.1, R45.1, R49.1, R53.1, TP5.1 (PAD_1), TP9.1 (PAD_1), U1.E10 (VCCO_0), U1.E11 (VCCBATT_0), U1.G12 (VCCAUX_[5_balls]), U1.H13 (VCCAUX), U1.K13 (VCCAUX), U1.M13 (VCCAUX), U1.P13 (VCCAUX), U1.R10 (VCCO_0), U1.R12 (M0_0), U3.6 (OUT_S), U3.9 (OUT), U3.10 (OUT), U7.8 (VCC_1.8_V), U8.13 (VCCB_1V8)
VCCINT_1V0: C2.1, C3.1, C4.1, C5.1, C6.1, C7.1, C8.1, C9.1, C10.1, C11.1, C89.1, C90.1, C91.1, C92.1, C93.1, R1.1, TP4.1 (PAD_1), U1.F7 (VCCINT_1V0), U1.F9 (VCCINT_1V0), U1.F11 (VCCBRAM/VCCINT_[21_balls]), U1.G8 (VCCINT_1V0), U1.G10 (VCCBRAM_1V0), U1.H7 (VCCINT_1V0), U1.H9 (VCCINT_1V0), U1.H11 (VCCBRAM_1V0), U1.J8 (VCCINT_1V0), U1.J12 (VCCINT_1V0), U1.K7 (VCCINT_1V0), U1.K11 (VCCINT_1V0), U1.L8 (VCCINT_1V0), U1.L12 (VCCINT_1V0), U1.M7 (VCCINT_1V0), U1.M11 (VCCINT_1V0), U1.N8 (VCCINT_1V0), U1.N10 (VCCINT_1V0), U1.N12 (VCCINT_1V0), U1.P9 (VCCINT_1V0), U1.P11 (VCCINT_1V0), U2.6 (OUT_S), U2.9 (OUT), U2.10 (OUT)
VCCO_1V5: C22.1, C23.1, C24.1, C25.1, C26.1, C27.1, C28.1, C29.1, C30.1, C31.1, C32.1, C33.1, C34.1, C35.1, C36.1, C37.1, C38.1, C39.1, C40.1, C42.1, C61.1, C63.1, C101.1, C105.1, L3.1, R7.1, R19.1, R25.1, R48.1, R50.1, R58.1, TP6.1 (PAD_1), U1.A16 (VCCO), U1.B13 (VCCO), U1.C10 (VCCO), U1.D17 (VCCO), U1.E14 (VCCO), U1.G18 (VCCO), U1.H15 (VCCO), U1.L6 (VCCO), U1.L16 (VCCO), U1.M3 (VCCO), U1.P7 (VCCO), U1.P17 (VCCO), U1.R4 (VCCO), U1.R14 (VCCO), U1.T1 (VCCO), U1.T11 (VCCO), U1.U8 (VCCO), U1.U18 (VCCO), U1.V5 (VCCO), U1.V15 (VCCO), U4.6 (OUT_S), U4.9 (OUT), U4.10 (OUT), U8.5 (DIR3_H), U8.14 (VCCA_1V5), U8.15 (DIR1_H), U8.16 (DIR2_H), U14.5 (VCC_1V5), U15.1 (VCCA), U15.5 (DIR)
VIN_3V3: C1.1, C12.1, C21.1, C44.1, C48.1, C75.1, C82.1, C83.1, C85.1, C102.1, C103.1, C208.1, J1.60, R3.1, R9.1, R12.1, R43.1, R47.1, R59.1, TP2.1 (PAD_1), U2.3 (EN), U2.12 (IN), U2.13 (IN), U2.14 (IN), U3.12 (IN), U3.13 (IN), U3.14 (IN), U4.12 (IN), U4.13 (IN), U4.14 (IN), U5.4 (BIAS), U6.4 (BIAS), U10.3 (VCC), U10.6 (VIN), U10.11 (VIN), U11.5 (VCC_3V3), U12.4 (VDD_3V3), U13.12 (IN), U13.13 (IN), U13.14 (IN), U16.6 (OUT_S), U16.9 (OUT), U16.10 (OUT)
VIN_5V: C206.1, C207.1, J3.19 (5V_IN), TP14.1 (PAD_1), U16.3 (EN), U16.12 (IN), U16.13 (IN), U16.14 (IN)

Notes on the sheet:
1. Function: MP5077 enables the local3.3V clock/support branch after core PG. VIN_3V3 from U16 (5 V cable input) feeds FPGA buck inputs and GTP LDO BIAS directly. The carrier port switch limits cable current.
2. Source / changes: Trenz TE0714-04-42I-7-L REV04(20Dec2022),p9 Q1/R52/C1/input-output bypass copied: https://www.trenz-electronic.de/trenzdownloads/Trenz_Electronic/Modules_and_Module_Carriers/3x4/TE0714/REV04/Documents/SCH-TE0714-04-42I-7-L.PDF MPS MP5077 Rev1.2(15Aug2023),p2 pinout,pp11-14 limi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
1. Function: U15 passes M15 EN_GTPWR_1V5 to U13 EN at3.3V. R58=4.99k pulls A HIGH by default; DIR HIGH selects A-to-B. R57=10k pulls B LOW when translator power is absent. C105/C106=100nF bypass both supply rails.
2. Source / changes: Codex voltage adaptation of Trenz TE0714 REV04 pp5,6,9: M15 EN_GTPWR,4.99k default pullup and two cascaded open-drain inverters. https://www.trenz-electronic.de/trenzdownloads/Trenz_Electronic/Modules_and_Module_Carriers/3x4/TE0714/REV04/Documents/SCH-TE0714-04-42I-7-L.PDF Tren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
1. Function: U1 / J1 / J2: Route116 active signals for eight1.5V ASICs through two60-contact mezzanines. J1.60 carries U16-regulated VIN_3V3; J2.60 remains reserved analog.
2. Source / changes: Codex custom ASIC interface; inherited V54/V62 pin contract preserved. ASIC_REFERENCE.md sections2-5; Chip_FPGA Interface.pptx slides13-17/25-28; Pins.xlsx. Trenz p5 I/O bank use adapted to ASIC allocation. https://www.trenz-electronic.de/trenzdownloads/Trenz_Electronic/Modules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
1. Function: J3 carries three GT recording TX pairs, regular-I/O commands, JTAG and 5 V power (contact 19 -> VIN_5V -> U16). TX0 connects to XEM; TX1/TX2 end open at carrier.
2. Source / changes: Codex custom HDMI map adapted from V3: 9/11 add TX2 via C204/C205; 12/14 move from GTP RX1 to U1 V3/V2 regular I/O. AMD DS181 v1.27.1 Table 50: CEXT=100 nF; C200-C205 are candidates. https://docs.amd.com/api/khub/documents/iAkxxTOk96ANLJqYf2hgrQ/content Unused RX1 A4/A3 grounde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
1. Function: U4: Generate1.5V for ASIC banks14/15/34, U8 A-side, Y2 and U15 A-side; enabled by core PG. PG participates in reset readiness.
2. Source / changes: Codex adaptation of Trenz p9 buck structure: separate1.5V converter retained for required ASIC interface. R7/R8 divider remains150k/100k,0.1%; U3PG->PG_CORE enable avoids GTP/1.5V dependency. https://www.trenz-electronic.de/trenzdownloads/Trenz_Electronic/Modules_and_Module_Car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
1. Function: ASIC-bank bypass: Bank14 C24-C29+C101=3x4.7u+4x470n; Bank15 C30-C35=2x4.7u+4x470n; Bank34 C36-C40=2x4.7u+3x470n. C42=47u shared1.5V bulk.
2. Source / changes: Trenz p7 bank populations restored: addedC1014.7u; removed extraC41470n. Common3.3V Bank0/14 network split for our1.8V/1.5V domains. https://www.trenz-electronic.de/trenzdownloads/Trenz_Electronic/Modules_and_Module_Carriers/3x4/TE0714/REV04/Documents/SCH-TE0714-04-42I-7-L.PDF 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
1. Function: L1/L2/C57/C58: Filter AUX1.8V for unused XADC; analog/reference inputs grounded to GNDADC.
2. Source / changes: Trenz p7 L10/L11/C62/C63 circuit retained with exact ferrites. Custom connector omits Trenz external ADC pair; unused-input grounding retained. https://www.trenz-electronic.de/trenzdownloads/Trenz_Electronic/Modules_and_Module_Carriers/3x4/TE0714/REV04/Documents/SCH-TE0714-04-4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
1. Function: U7/U8: 16MiB 1.8V SPI NOR flash (Winbond W25Q128JWUUIQ, 4x3mm USON-8) and SN74AVC4T774RSV SPIx1 translation. Bank14 remains1.5V; initialCONFIGRATE3MHz/QE0/3-byte addresses.
2. Source / changes: Adapted from V5 IS25WP128F-JKLE (6x5mm WSON-8) to Winbond W25Q128JWUUIQ (4x3mm USON-8, pkg code UU, 0.80mm pitch; AMD UG908 w25q128fw/jw family) to save 60% flash area for V6 size reduction. R19/R22 4.99k; pullups 1.8V. https://www.winbond.com/resource-files/w25q128jw%20revg%20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
1. Function: Y2:25MHz fabric clock drives N3 SRCC at1.5V. L3 filters1.5V; C88=100nF; R44=33R output damping.
2. Source / changes: Trenz p5 U8/L2/C24/R23 structure adapted: SiT1615 1.5V replaces SiT8008 1.8V; T14 occupied by ASIC2 clock so useN3. C88 retained100n per SiTime; R44 exact Trenz RC0201FR-0733RL restored. https://www.trenz-electronic.de/trenzdownloads/Trenz_Electronic/Modules_and_Module_Carriers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
1. Function: GTP bypass C51-C56: each analog rail now4.7uF+2x470nF. R16=100R connects MGTRREF to MGTAVTT.
2. Source / changes: Trenz p7 nominal/value/package/tolerance restored: C52/C53/C55/C56 100n->470n; C51/C54 4.7u20%; R16 selected100R0.1%25ppm ERA1A meets source100R1%TK100 class. Selected compatible Murata/Yageo candidates; Trenz exact MPNs not all disclosed. https://www.trenz-electronic.de/trenzd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
1. Function: Y1 supplies125MHz LVDS through C78/C79=100nF to REFCLK1P/N. L4 filters switched3.3V; C80=470nF and C81=100nF bypass it. R56=100R loads OSC125_P/N before the coupling capacitors; OE HIGH, pin2 NC.
2. Source / changes: Trenz TE0714-04-42I-7-L REV04 p6:125MHz LVDS U2, L1 ferrite, C10=470nF, R1=100R and C134/C135=100nF coupling. https://www.trenz-electronic.de/trenzdownloads/Trenz_Electronic/Modules_and_Module_Carriers/3x4/TE0714/REV04/Documents/SCH-TE0714-04-42I-7-L.PDF Adapted by Codex: Y1=AX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
01. FPGA I/O + ASIC INTERFACES + 25 MHz CLOCK | Trenz p5
02. GTP CHANNELS + 125 MHz REFERENCE | Trenz p6
03. FLASH + SPI TRANSLATION | Trenz p6 adaptation
04. CONFIGURATION + RESET OUTPUTS | Trenz p7 roles
05. FPGA SUPPLY PINS + BYPASS + XADC | Trenz p7
06. REGULATORS + READINESS SUPERVISOR | Trenz p9 roles
1. Function: U1 configuration: Master SPI001,CFGBVS GND, Bank0/JTAG1.8V; ASIC banks1.5V. PROGRAM_B and INIT_B reset independently. VCCBATT E11 now AUX1.8V.
2. Source / changes: Trenz p7 values restored where compatible: R17/R18/R19/R22=4.99k; E11 GND->AUX. Mode ties/1.8V rails and x1 flash remain agreed adaptations. https://www.trenz-electronic.de/trenzdownloads/Trenz_Electronic/Modules_and_Module_Carriers/3x4/TE0714/REV04/Documents/SCH-TE0714-04-42I-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
1. Function: Bank0 bypass C59,C94-C100:47uF+3x4.7uF+4x470nF at1.8V, separate from1.5V Bank14.
2. Source / changes: Codex split of Trenz p7 shared Bank0/14 network to preserve agreed voltage domains; addedC94-C100, C59 exact Trenz CC0805MKX5R5BB476. https://www.trenz-electronic.de/trenzdownloads/Trenz_Electronic/Modules_and_Module_Carriers/3x4/TE0714/REV04/Documents/SCH-TE0714-04-42I-7-L.PDF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
1. Function: U11 holds PROGRAM_B and INIT_B LOW through two independent open-drain outputs; R17/R18 release them to 1.8 V. U14 drives the 1.5 V active-low U8 enable. C82/C63 are local bypass.
2. Source / changes: Correspondence: Trenz p7 D1/D2 reset-hold functions -> U11; U14 is added for our U8 flash translator, not Trenz boot-mode inverter U9. V64 electrical network unchanged. Codex voltage adaptation of Trenz p7 D1/D2 reset function; inherited V61 agreed flash/U8 support retained. Tr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
1. Function: TP1-TP13: Expose ground, U16 VIN_3V3, switched3.3V and local rails/status. Virtual power flags declare sources to ERC.
2. Source / changes: Codex debug additions retained;13 custom0.6mm pads versus Trenz21 pads0.8mm. TP10 now finalAVCC-PG; TP3 switchedbranch. No physical testpad datasheet; no V65 PCB. Probe loading/access unverified.
1. Function: U2: Generate1.0V core/BRAM. PG_CORE_1V0 enables U3,U4 and U10. C1/C2 are22uF input/output.
2. Source / changes: Trenz TE0714 REV04 p9 U1 core-buck structure restored at compatible values/packages; our U2 is MPM3834C. MPM3834C Rev1.01, Fig4 p17 and feedback pp13-14. Our R1/R2=200k/301k; R3=4.99k; C3=22pF retains higher50V NP0 candidate. https://www.trenz-electronic.de/trenzdownloads/Trenz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
1. Function: U3: Generate1.8V AUX/Bank0/flash/JTAG after core PG. R5 and R55 are200k each in parallel, equivalent100k. PG unused.
2. Source / changes: Trenz TE0714 REV04 p9 U3 AUX-buck divider restored: our R4=200k, R5=200k and added R55=200k; removed R6 AUX-PG pullup. Our U4 now follows core PG and U13 follows translated firmware enable. https://www.trenz-electronic.de/trenzdownloads/Trenz_Electronic/Modules_and_Module_Carri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

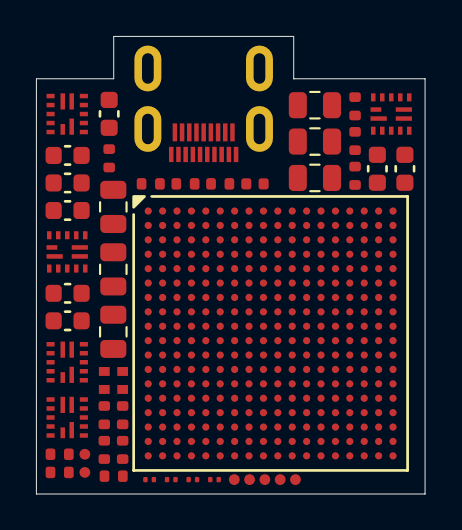
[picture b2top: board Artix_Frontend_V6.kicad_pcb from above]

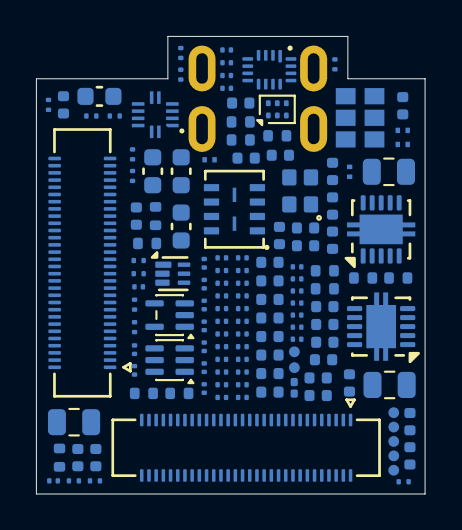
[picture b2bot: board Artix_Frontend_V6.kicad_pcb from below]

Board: 10 copper layers, 21.6 x 25.4 mm, 185 parts (136 on the bottom side), 191 nets, no tracks yet.
